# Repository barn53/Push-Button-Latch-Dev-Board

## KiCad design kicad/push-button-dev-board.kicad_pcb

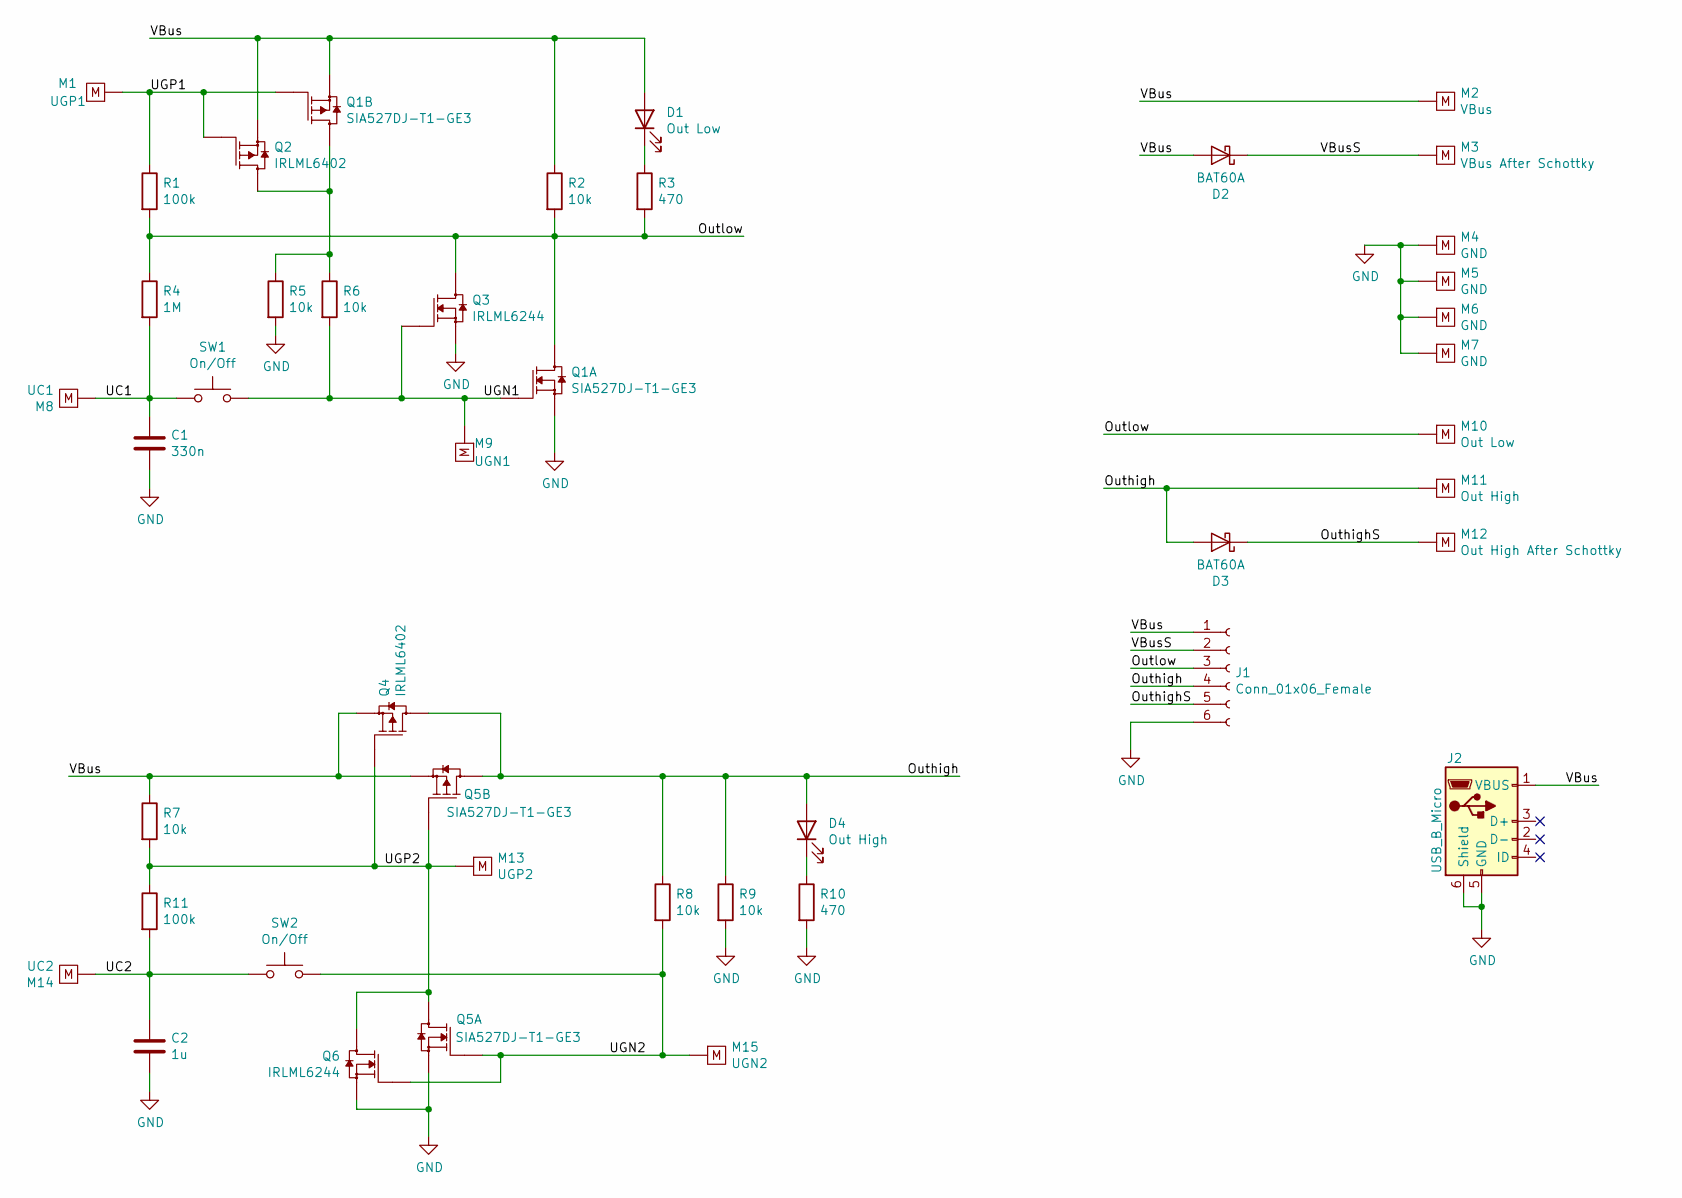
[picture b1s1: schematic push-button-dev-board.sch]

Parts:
C1: 330n; C_0805_2012Metric
C2: 1u; C_0805_2012Metric
D1: Out Low; LED_0805_2012Metric_Castellated
D2, D3: BAT60A; D_SOD-323F
D4: Out High; LED_0805_2012Metric_Castellated
J1: Conn_01x06_Female; PinSocket_1x06_P2.54mm_Vertical
J2: USB_B_Micro; MicroUSB_through_hole_fixing
M1: UGP1; Measure_Point
M2: VBus; Measure_Point
M3: VBus After Schottky; Measure_Point
M4, M5, M6, M7: GND; Measure_Point
M8: UC1; Measure_Point
M9: UGN1; Measure_Point
M10: Out Low; Measure_Point
M11: Out High; Measure_Point
M12: Out High After Schottky; Measure_Point
M13: UGP2; Measure_Point
M14: UC2; Measure_Point
M15: UGN2; Measure_Point
Q1, Q5: SIA527DJ-T1-GE3; PowerPAK_SC70-6L_Dual
Q2, Q4: IRLML6402; SOT-23
Q3, Q6: IRLML6244; SOT-23
R1, R11: 100k; R_0805_2012Metric
R2, R5, R6, R7, R8, R9: 10k; R_0805_2012Metric
R3, R10: 470; R_0805_2012Metric
R4: 1M; R_0805_2012Metric
SW1, SW2: On/Off; SMD_Push_Button_vertical

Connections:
/Outhigh: D3.2 (A), D4.2 (A), J1.4, M11.1, Q4.3 (D), Q5.3 (D2), R8.1, R9.1
/OuthighS: D3.1 (K), J1.5, M12.1
/Outlow: J1.3, M10.1, Q1.6 (D1), Q3.3 (D), R1.2, R2.2, R3.2, R4.1
/UC1: C1.1, M8.1, R4.2, SW1.1
/UC2: C2.1, M14.1, R11.2, SW2.1
/UGN1: M9.1, Q1.2 (G1), Q3.1 (G), R6.2, SW1.2
/UGN2: M15.1, Q5.2 (G1), Q6.1 (G), R8.2, SW2.2
/UGP1: M1.1, Q1.5 (G2), Q2.1 (G), R1.1
/UGP2: M13.1, Q4.1 (G), Q5.5 (G2), Q5.6 (D1), Q6.3 (D), R7.2, R11.1
/VBus: D1.2 (A), D2.2 (A), J1.1, J2.1 (VBUS), M2.1, Q1.4 (S2), Q2.2 (S), Q4.2 (S), Q5.4 (S2), R2.1, R7.1
/VBusS: D2.1 (K), J1.2, M3.1
GND: C1.2, C2.2, J1.6, J2.5 (GND), J2.6 (Shield), M4.1, M5.1, M6.1, M7.1, Q1.1 (S1), Q3.2 (S), Q5.1 (S1), Q6.2 (S), R5.2, R9.2, R10.2
unnamed: D1.1 (K), R3.1
unnamed: D4.1 (K), R10.1
unnamed: Q1.3 (D2), Q2.3 (D), R5.1, R6.1

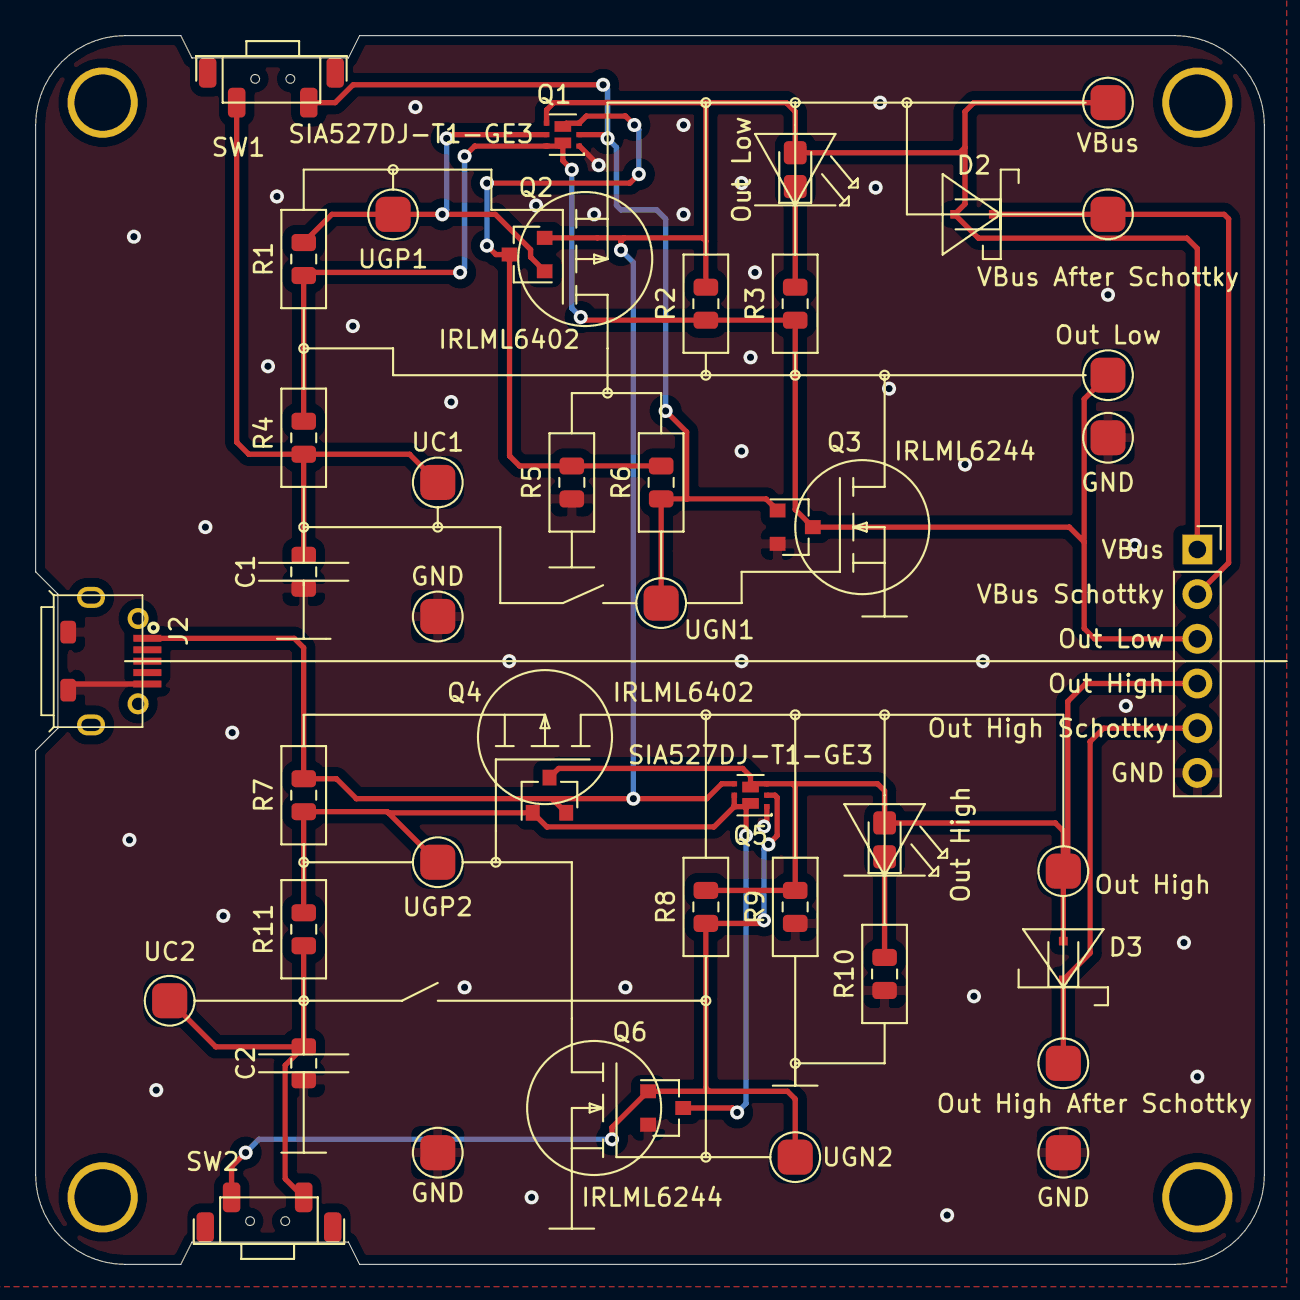
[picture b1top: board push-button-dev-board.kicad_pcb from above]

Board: 2 copper layers, 69.9 x 69.9 mm, 43 parts (1 on the bottom side), 15 nets.

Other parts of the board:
QR*****: https://github.com/gerdmuller/Push-Button-Latch-D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; //github.com/gerdmuller/Push-Button-Latch-Dev-Board

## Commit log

2020-10-25 Finished first revision rev.A
2021-01-19 minor
